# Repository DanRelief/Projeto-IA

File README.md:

# Otimizador de Posicionamento e Roteamento de PCBs com Algoritmo Genético no KiCad

Este repositório contém uma solução automatizada desenvolvida em Python para otimização do posicionamento (*placement*) e roteamento de componentes em Placas de Circuito Impresso (PCBs). Utilizando **Algoritmos Genéticos (AG)** integrados à API nativa do **KiCad (`pcbnew`)**, o projeto visa atender a regras de negócio e boas práticas de projeto eletrônico, garantindo menor distância entre componentes críticos e prevenindo colisões físicas.

---

## 📌 Visão Geral do Projeto

No desenvolvimento de hardware, a distribuição física dos componentes afeta diretamente o desempenho eletrônico, a integridade do sinal, a facilidade de roteamento e os custos de fabricação. A automação desse processo por meio de algoritmos evolucionários reduz a necessidade de intervenção manual ostensiva, permitindo otimizar requisitos como:

* **Proximidade Crítica:** Aproximação de componentes sensíveis a ruídos ou alta frequência (ex.: cristais osciladores e capacitores de desacoplamento) aos picos/pinos dos microcontroladores (MCU).

* **Design for Manufacturing (DFM) & Colisões:** Aplicação de margens de segurança para evitar sobreposição geométrica e invasão de footprints.

* **Roteamento Eficiente:** Otimização prévia do layout para simplificar a etapa posterior de roteamento de trilhas (*routing*) realizada por ferramentas como o *Freerouting*.

---

## 🛠️ Tecnologias e Ferramentas Utilizadas

* **Linguagem:** Python 3.11+.

* **EDAs / Suporte de Layout:** KiCad 10.0 (aplicando API `pcbnew`).

* **Bibliotecas Python:** `math`, `random`, `dataclasses`, `sys`, `importlib`.

* **Roteamento de Trilhas:** Integration via arquivo `.dsn` (Specctra) com *Freerouting*.

---

## 🧬 Arquitetura da Solução (Algoritmo Genético)

O motor evolutivo foi construído do zero, implementando as fases do AG adaptadas ao espaço bidimensional da PCB:

1. **Representação (Cromossomo):** Mapeia os componentes móveis com coordenadas e rotações: $(X, Y, \text{Orientação} \in \{0^\circ, 90^\circ, 180^\circ, 270^\circ\})$.

2. **População Inicial:** Gerada estocasticamente respeitando o contorno (*outline*) e limites da placa.

3. **Função de Aptidão (*Fitness Function*):**
* **Objetivo:** Maximizar a aptidão (minimizar custo total).

* **Custo de Distância:** Calcula a distância euclidiana de componentes críticos ao MCU ($U1$).

* **Penalidade de Colisão:** Aplica uma penalidade severa (ex.: $-1000.0$) caso a distância entre componentes fique abaixo da margem de segurança física (ex.: $7.5\text{ mm}$).

4. **Operadores Genéticos:**
* **Seleção:** Método de Torneio ($k=3$).

* **Recombinação (Crossover):** *Crossover Uniforme* trocando parâmetros de coordenadas entre pais com 50% de probabilidade.

* **Mutação:** Deslocamento estocástico nos eixos $X$ e $Y$ com alteração ocasional de rotação.

## 🚀 Como Executar

### Pré-requisitos

* KiCad v7 (ou superior com suporte para `pcbnew`) instalado.

* Arquivo do projeto e script salvos na máquina local (incluindo arquivos CAD da PCB e demais libs do projeto **em um mesmo diretório**).

### Execução no Console Python Interno do KiCad

1. Abra a placa no **KiCad PCB Editor**.

2. Acesse o console interativo do Python: **Ferramentas > Console de Scripting Python**.

3. Execute os seguintes comandos no console para rodar o algoritmo e ver as mudanças em tempo real na tela:

```python
import sys
import pcbnew

# Adicione o caminho do diretório onde o arquivo script_IA.py está localizado
sys.path.append(r"C:\Caminho\Para\Seu\Projeto")

# Importa o módulo do script
import script_IA

# Captura a placa ativa aberta no KiCad e executa a otimização
board = pcbnew.GetBoard()
script_IA.run_ga_placement(board)

```

---

## 🧪 Validação e Testes Modulares

A validação da lógica do AG concentrou-se na **regra isolada do Cristal Oscilador ($Y1$) e Microcontrolador ($U1$)**:

* **Objetivo:** Otimizar o posicionamento de $Y1$ para ficar o mais próximo possível de $U1$, respeitando a margem física de segurança.

* **Resultados:** Observou-se a convergência do algoritmo ao longo das gerações (com decréscimo na distância euclidiana) e a atualização automática da tela gráfica do KiCad através do comando `pcbnew.Refresh()`.

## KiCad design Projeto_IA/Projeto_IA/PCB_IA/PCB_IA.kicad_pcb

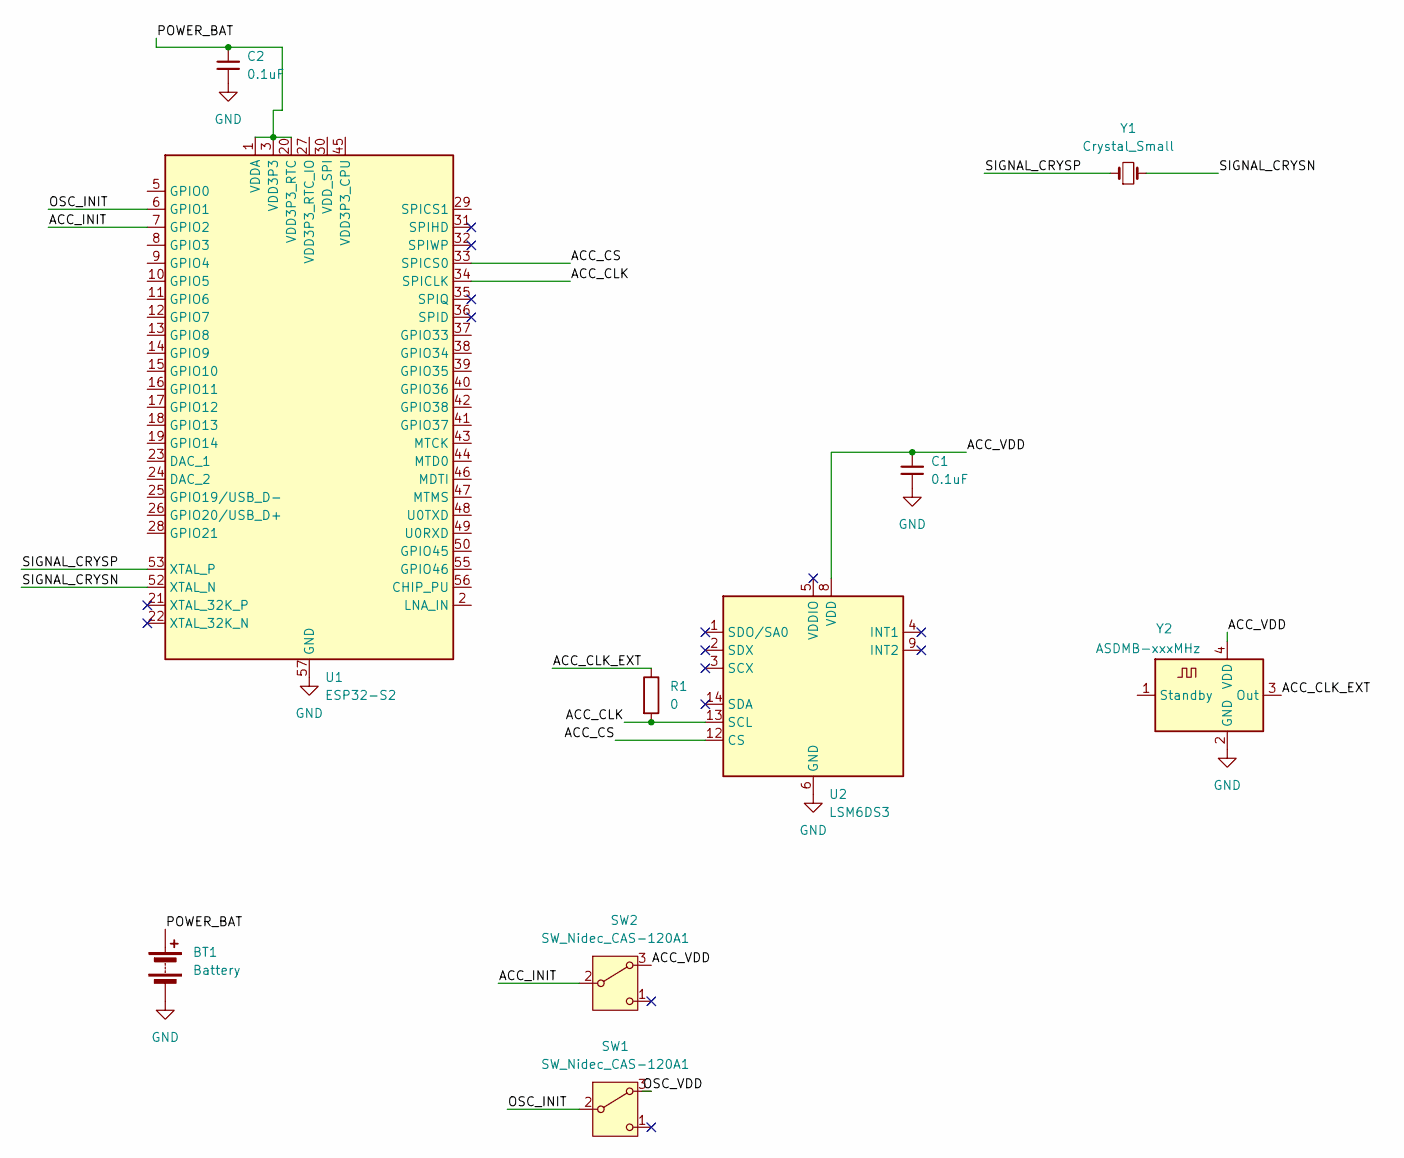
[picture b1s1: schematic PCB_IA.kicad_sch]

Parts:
BT1: Battery; Texas_DRC0010J_ThermalVias
C1, C2: 0.1uF; C_01005_0402Metric
R1: 0; R_01005_0402Metric
SW1, SW2: SW_Nidec_CAS-120A1; Nidec_Copal_CAS-120A
U1: ESP32-S2; QFN-56-1EP_7x7mm_P0.4mm_EP4x4mm
U2: LSM6DS3; LGA-14_3x2.5mm_P0.5mm_LayoutBorder3x4y
Y1: Crystal_Small; Crystal_DS10_D1.0mm_L4.3mm_Horizontal
Y2: ASDMB-xxxMHz; Oscillator_SMD_Abracon_ASDMB-4Pin_2.5x2.0mm

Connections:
/ACC_CLK: R1.2, U1.34 (SPICLK), U2.13 (SCL)
/ACC_CLK_EXT: R1.1, Y2.3 (Out)
/ACC_CS: U1.33 (SPICS0), U2.12 (CS)
/ACC_INIT: SW2.2 (B), U1.7 (GPIO2)
/ACC_VDD: C1.1, SW2.3 (A), U2.8 (VDD), Y2.4 (VDD)
/OSC_INIT: SW1.2 (B), U1.6 (GPIO1)
/OSC_VDD: SW1.3 (A)
/POWER_BAT: BT1.1 (+), C2.1, U1.1 (VDDA), U1.3 (VDD3P3), U1.4 (VDD3P3), U1.20 (VDD3P3_RTC), U1.51 (VDDA), U1.54 (VDDA)
/SIGNAL_CRYSN: U1.52 (XTAL_N), Y1.2
/SIGNAL_CRYSP: U1.53 (XTAL_P), Y1.1
GND: BT1.2 (-), C1.2, C2.2, U1.57 (GND), U2.6 (GND), U2.7 (GND), Y2.2 (GND)

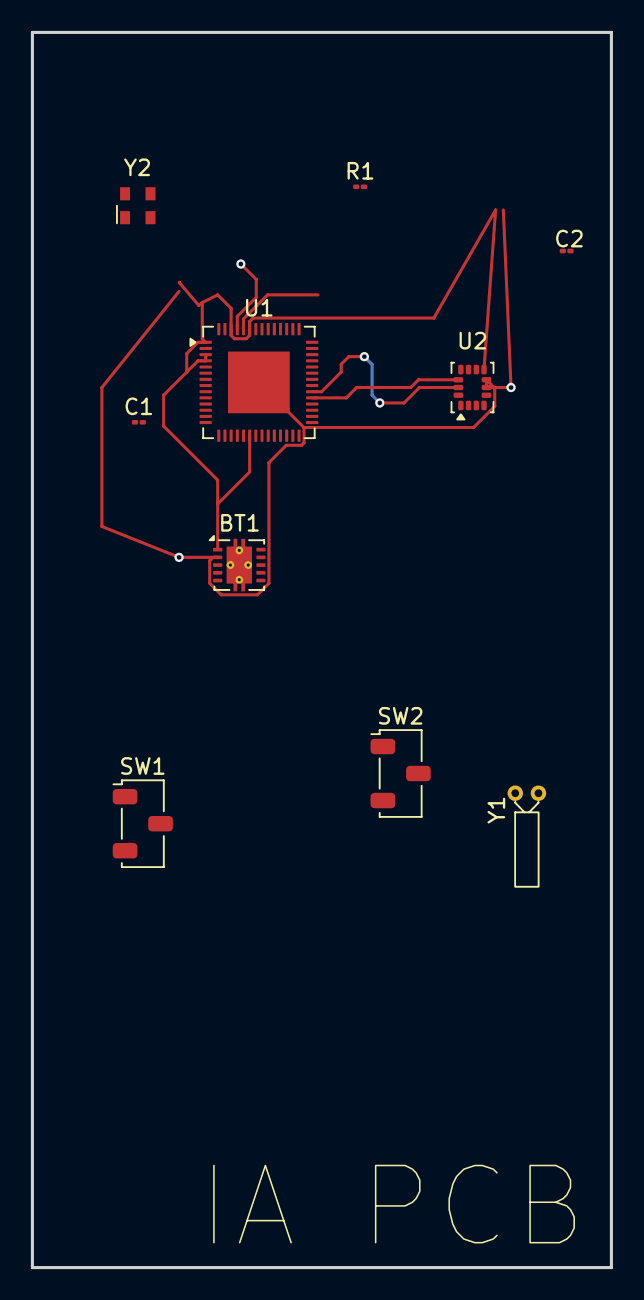
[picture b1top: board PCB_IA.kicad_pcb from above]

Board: 2 copper layers, 37.5 x 80.0 mm, 10 parts (0 on the bottom side), 10 nets.
